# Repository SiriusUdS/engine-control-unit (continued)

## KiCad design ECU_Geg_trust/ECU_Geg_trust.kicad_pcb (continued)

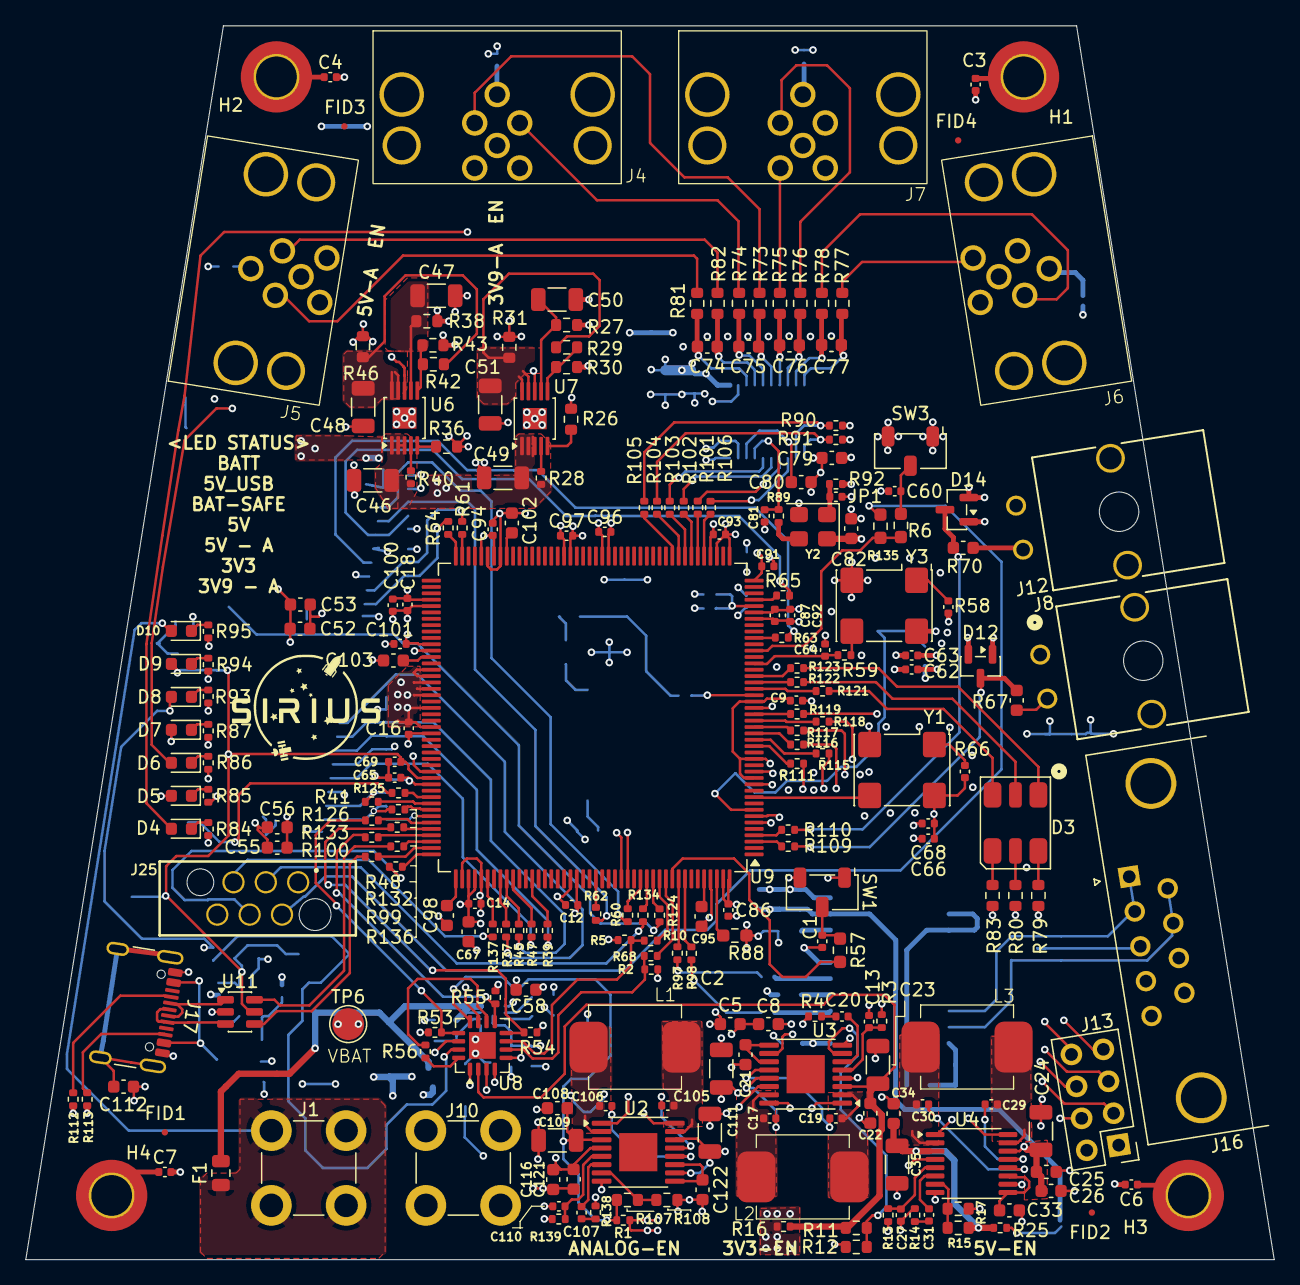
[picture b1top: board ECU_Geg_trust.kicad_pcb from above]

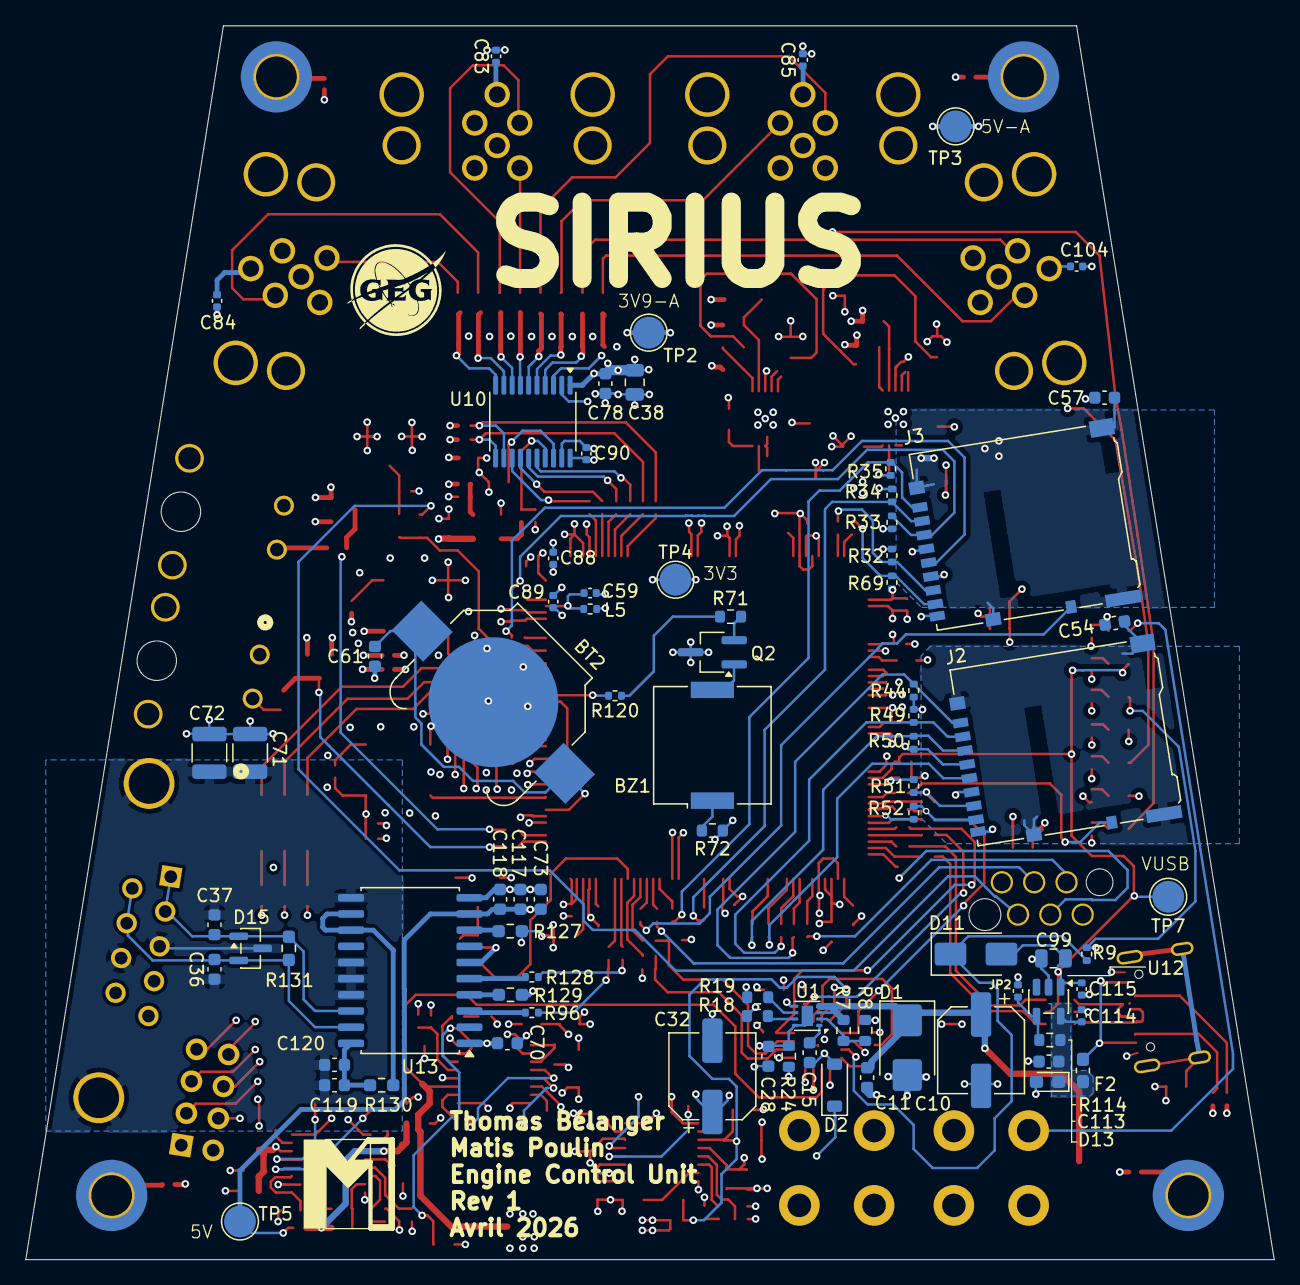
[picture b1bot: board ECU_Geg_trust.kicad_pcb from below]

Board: 6 copper layers, 98.0 x 96.9 mm, 321 parts (80 on the bottom side), 224 nets.

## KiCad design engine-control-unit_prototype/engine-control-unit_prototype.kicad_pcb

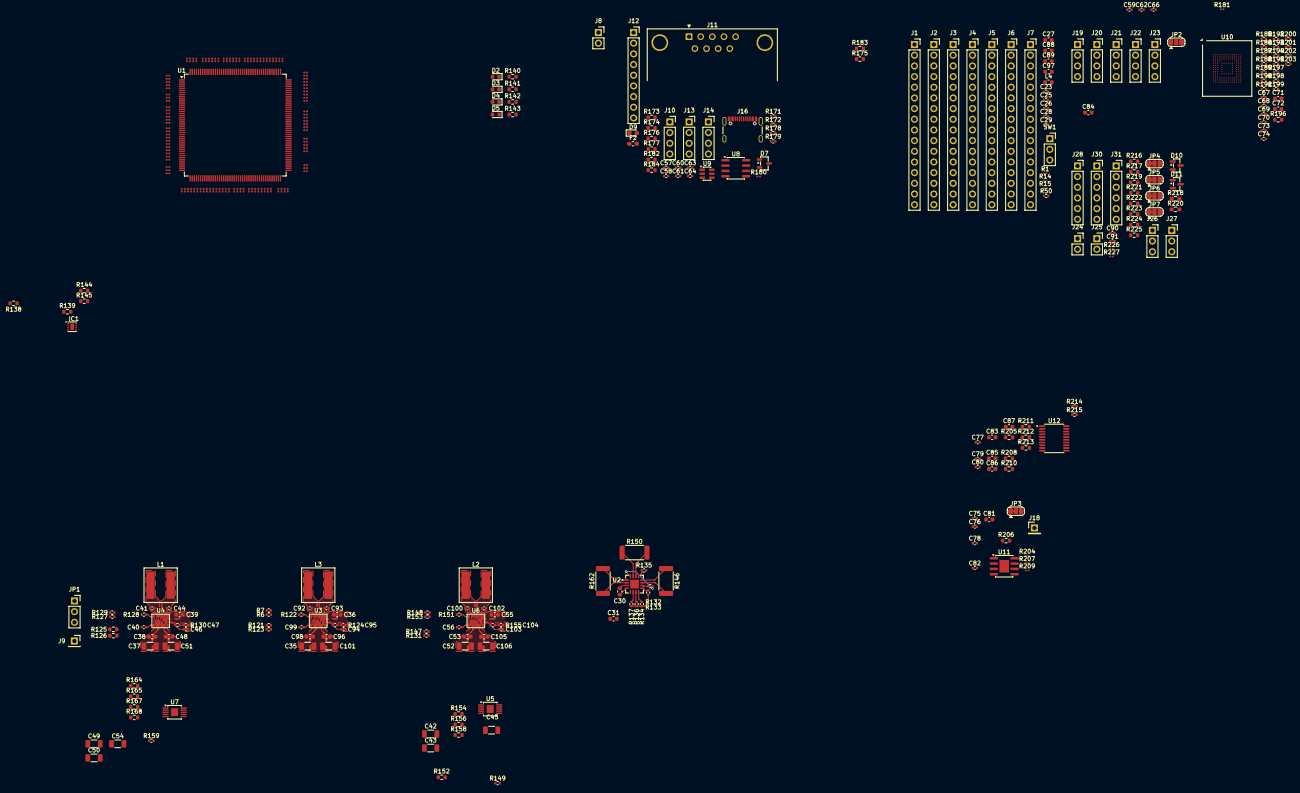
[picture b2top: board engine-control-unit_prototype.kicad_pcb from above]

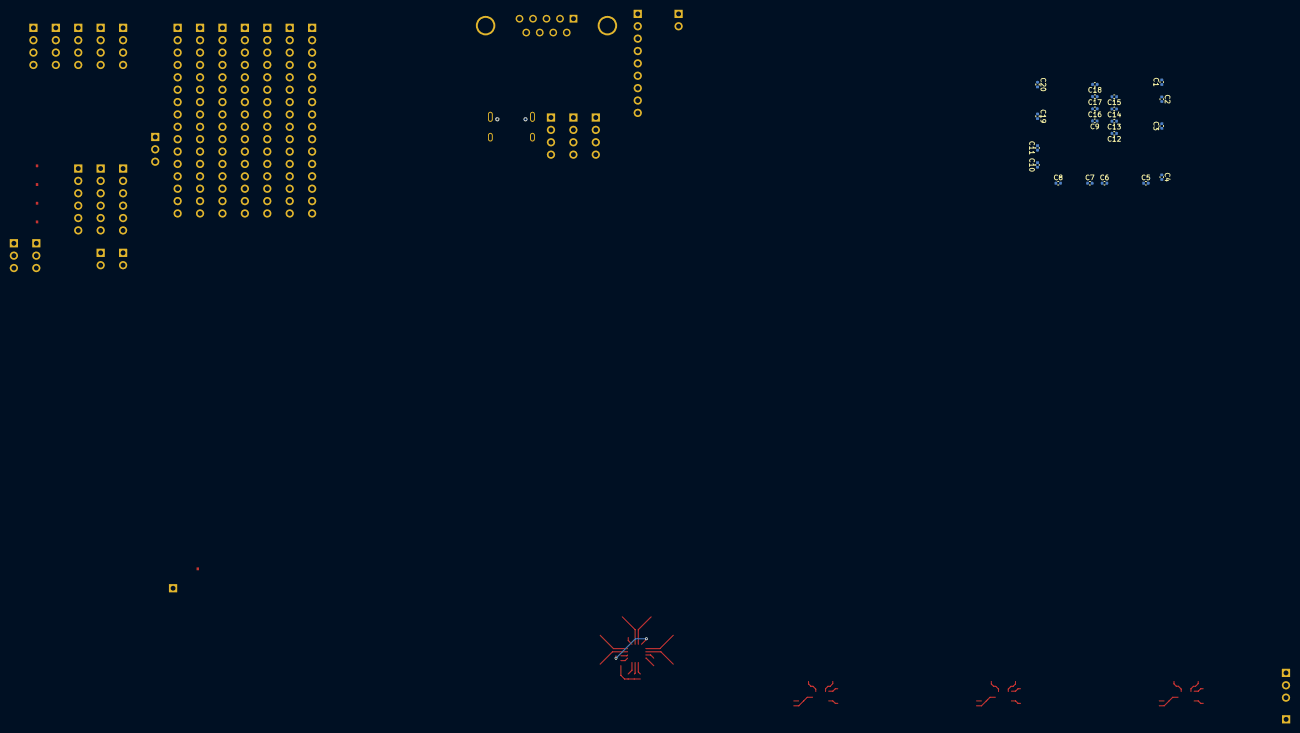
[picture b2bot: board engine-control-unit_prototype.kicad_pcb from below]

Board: 2 copper layers, 381 parts (20 on the bottom side), 374 nets.

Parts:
C1, C2, C3, C4, C5, C6, C7, C8, C9, C10, C11, C12, C13, C14, C15, C16, C17, C18, C19, C20, C23, C25, C26, C28, C29, C57, C58: 100n; C_0402_1005Metric
C27: 2.2u ESR < 600m; C_0603_1608Metric
C30: 0u1; C_0603_1608Metric
C31, C71, C84: 10u; C_0603_1608Metric
C35, C37, C42, C43, C45, C51, C52, C101, C106: C; C_1206_3216Metric
C36, C38, C39, C48, C53, C55, C96, C98, C105: C; C_0603_1608Metric
C40, C41, C44, C56, C92, C93, C99, C100, C102: C; C_0402_1005Metric
C46, C94, C103: 100p; C_0402_1005Metric
C47, C59, C76, C78, C82, C95, C104: ?; C_0402_1005Metric
C49, C50, C54: 4u7; C_1206_3216Metric
C60, C61: DNF; C_0402_1005Metric
C62, C63, C64, C66, C67, C68, C69, C70, C73, C74, C75, C90, C91: 0u1; C_0402_1005Metric
C72: 2.2u; C_0603_1608Metric
C77: 10n; C_0402_1005Metric
C79, C80: 1u; C_0402_1005Metric
C81: DNF; C_0603_1608Metric
C83, C85, C87: 10n; C_0603_1608Metric
C86: 220n; C_0603_1608Metric
C88, C89: 2u2; C_0603_1608Metric
C97: 4u7; C_0603_1608Metric
D2: VBATT+; LED_0603_1608Metric
D3: VDD_10V; LED_0603_1608Metric
D4: VDD_3V3; LED_0603_1608Metric
D5: VDDA_3V3; LED_0603_1608Metric
D7: DNF; SOT-23-3
D9: 6.4V; D_0603_1608Metric_Pad1.05x0.95mm_HandSolder
D10, D11: BAV99; SOT-23
F2: Polyfuse; Fuse_0603_1608Metric_Pad1.05x0.95mm_HandSolder
IC1: TPS259573DSGR; WSON-8-1EP_2x2mm_P0.5mm_EP0.9x1.6mm
J1: PORT_G; PinSocket_1x16_P2.54mm_Vertical
J2: PORT_E; PinSocket_1x16_P2.54mm_Vertical
J3: PORT_F; PinSocket_1x16_P2.54mm_Vertical
J4: PORT_A; PinSocket_1x16_P2.54mm_Vertical
J5: PORT_B; PinSocket_1x16_P2.54mm_Vertical
J6: PORT_D; PinSocket_1x16_P2.54mm_Vertical
J7: PORT_C; PinSocket_1x16_P2.54mm_Vertical
J8: 2S_18650; PinSocket_1x02_P2.54mm_Vertical
J9: EXT_BATT; PinSocket_1x01_P2.54mm_Vertical
J10: I2C; PinSocket_1x04_P2.54mm_Vertical
J11: CANFD; DSUB-9_Pins_Horizontal_P2.77x2.84mm_EdgePinOffset7.70mm_Hou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
J12: ADXL345; PinSocket_1x09_P2.54mm_Vertical
J13: MAG_CONN_1; PinSocket_1x04_P2.54mm_Vertical
J14: MAG_CONN_2; PinSocket_1x04_P2.54mm_Vertical
J16: USB_C_Receptacle_USB2.0_man; USB_C_Receptacle_GCT_USB4105-xx-A_16P_TopMnt_Horizontal
J18: VREF; PinHeader_1x01_P2.54mm_Vertical
J19: PT1; PinSocket_1x04_P2.54mm_Vertical
J20: PT2; PinSocket_1x04_P2.54mm_Vertical
J21: PT3; PinSocket_1x04_P2.54mm_Vertical
J22: PT4; PinSocket_1x04_P2.54mm_Vertical
J23: PT5; PinSocket_1x04_P2.54mm_Vertical
J24: HEATER_IPA; PinSocket_1x02_P2.54mm_Vertical
J25: HEATER_NOS; PinSocket_1x02_P2.54mm_Vertical
J26: VALVE_IPA; PinSocket_1x03_P2.54mm_Vertical
J27: VALVE_NOS; PinSocket_1x03_P2.54mm_Vertical
J28: NOS ENCODER; PinSocket_1x06_P2.54mm_Vertical
J30: IPA ENCODER; PinSocket_1x06_P2.54mm_Vertical
J31: VCTR_CONN; PinSocket_1x06_P2.54mm_Vertical
JP1: BATT; PinSocket_1x03_P2.54mm_Vertical
JP2: 3V3 / 10V; SolderJumper-3_P1.3mm_Open_RoundedPad1.0x1.5mm
JP3: PIN / GND; SolderJumper-3_P1.3mm_Bridged12_RoundedPad1.0x1.5mm
JP4, JP5, JP6, JP7: CONN / BOARD; SolderJumper-3_P1.3mm_Bridged12_RoundedPad1.0x1.5mm
L1, L2, L3: L; L_Coilcraft_XAL7070-XXX
L4: L_Ferrite; L_0603_1608Metric
R1, R2, R3, R4, R5, R8, R9, R10, R11, R12, R13, R14, R15, R16, R17, R18, R19, R20, R21, R22, R23, R24, R25, R26, R27, R28, R29, R30, R31, R32, R33, R34, R35, R36, R37, R38, R39, R40, R41, R42, R43, R44, R45, R46, R47, R48, R49, R51, R52, R53, R54, R55, R56, R57, R58, R59, R60, R61, R62, R63, R64, R65, R66, R67, R68, R69, R70, R71, R72, R73, R74, R75, R76, R77, R78, R79, R80, R81, R82, R83, R84, R85, R86, R87, R88, R89, R90, R91, R92, R93, R94, R95, R96, R97, R98, R99, R100, R101, R102, R103, R104, R105, R106, R107, R108, R109, R110, R111, R112, R113, R114, R115, R116, R117, R118, R119, R120, R180, R181, R204, R207, R209, R226, R227: 0; R_0201_0603Metric
R6, R7, R50, R131, R147: R_US; R_0402_1005Metric
R121, R123, R127, R129, R148, R153: 2k20; R_0402_1005Metric
R122, R128, R151: 0; R_0402_1005Metric
R124, R130, R155: 27k4; R_0402_1005Metric
R125, R126, R138, R139, R144, R145, R152, R154, R156, R158, R184: R_US; R_0603_1608Metric
R132, R133, R134, R135, R136, R137, R185, R186, R187, R188, R189, R190, R191, R192, R193, R194, R195, R197, R198, R199, R200, R201, R202, R203: 10k; R_0402_1005Metric
R140, R141, R142, R143, R196, R206, R216, R217, R219, R221, R222, R223: ?; R_0603_1608Metric
R146, R150, R162: 10m; R_2512_6332Metric
R149, R159: 200k; R_0402_1005Metric
R164: 453k; R_0603_1608Metric
R165: 510; R_0603_1608Metric
R167: 33k2; R_0603_1608Metric
R168: 49k9; R_0603_1608Metric
R171, R172, R178, R179, R214, R215: 1k; R_0402_1005Metric
R173, R174, R175: 0; R_0603_1608Metric
R176, R177: 60; R_0603_1608Metric
R182, R183: 5.1k; R_0603_1608Metric
R205, R208, R210, R211, R212, R213, R224, R225: 1k; R_0603_1608Metric
R218, R220: 10k; R_0603_1608Metric_Pad0.98x0.95mm_HandSolder
SW1: BOOT; PinSocket_1x03_P2.54mm_Vertical
U1: STM32H747II; LQFP-176_24x24mm_P0.5mm
U2: INA3221; Texas_RGV0016A_VQFN-16-1EP_4x4mm_P0.65mm_EP2.1x2.1mm
U3, U4, U6: TPS55285; WQFN-HR - 15
U5, U7: LT3042xMSE; MSOP-10-1EP_3x3mm_P0.5mm_EP1.68x1.88mm
U8: TCAN337G; SOIC-8_3.9x4.9mm_P1.27mm
U9: USBLC6-2SC6; SOT-23-6
U10: LFBGA-153_11.5x13mm_Layout14x14_P0.5mm
U11: INA826; SOIC-8-1EP_3.9x4.9mm_P1.27mm_EP2.29x3mm
U12: ADS131M04xPW; TSSOP-20_4.4x6.5mm_P0.65mm

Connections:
+BATT1: D2.2 (A), J8.1, J24.1, J25.1, R216.1, R217.1
/ADC/+IN1: J19.2, R204.2
/ADC/+IN2: C77.2, J20.2, R205.2
/ADC/+IN3: C83.2, J21.2, R210.2
/ADC/+IN4: C85.2, J22.2, R212.2
/ADC/+IN5: C87.2, J23.2, R214.2
/ADC/-IN1: J19.3, R209.2
/ADC/-IN2: C77.1, J20.3, R208.2
/ADC/-IN3: C83.1, J21.3, R211.2
/ADC/-IN4: C85.1, J22.3, R213.2
/ADC/-IN5: C87.1, J23.3, R215.2
/ADC/PT1: C81.2, R207.1
/BOOT0: SW1.2 (B), U1.167 (BOOT0)
/COMMUNICATION/ADXL_SCL: J12.9, R179.2
/COMMUNICATION/ADXL_SDA: J12.8, R178.2
/COMMUNICATION/CANH: C60.2, D7.1 (K), J11.7, J13.2, J14.2, R177.1, U8.7 (CANH)
/COMMUNICATION/CANL: C61.2, D7.2 (K), J11.2, J13.3, J14.3, R176.1, U8.6 (CANL)
/COMMUNICATION/I2C_SCL: J10.4, R172.2
/COMMUNICATION/I2C_SDA: J10.3, R171.2
/COMMUNICATION/TCAN_STBY: R175.1, U8.8 (S)
/COMMUNICATION/USB_D+: J16.A6 (D+), J16.B6 (D+), U9.3 (I/O2), U9.4 (I/O2)
/COMMUNICATION/USB_D-: J16.A7 (D-), J16.B7 (D-), U9.1 (I/O1), U9.6 (I/O1)
/CONTROL/IPA_DATA: D10.3 (K), J26.1, JP4.2 (C), JP4.3 (B), R218.1
/CONTROL/IPA_DATA_CONN: J31.2, JP4.1 (A)
/CONTROL/IPA_HEAT: JP6.2 (C), JP6.3 (B), R219.1
/CONTROL/IPA_HEAT_CONN: J31.4, JP6.1 (A)
/CONTROL/NOS_DATA: D11.3 (K), J27.2, JP5.2 (C), JP5.3 (B), R220.1
/CONTROL/NOS_DATA_CONN: J31.3, JP5.1 (A)
/CONTROL/NOS_HEAT: JP7.2 (C), JP7.3 (B), R221.1
/CONTROL/NOS_HEAT_CONN: J31.5, JP7.1 (A)
/NRST: R50.2, U1.33 (NRST)
/POWER/EFUSE_FLT: IC1.6 (~FLT), R139.1
/POWER/L1_L: C41.1, L1.1, U4.6 (SW1)
/POWER/L1_R: C44.1, L1.2, U4.8 (SW2)
/POWER/L2_L: C100.1, L2.1, U6.6 (SW1)
/POWER/L2_R: C102.1, L2.2, U6.8 (SW2)
/POWER/L3_L: C92.1, L3.1, U3.6 (SW1)
/POWER/L3_R: C93.1, L3.2, U3.8 (SW2)
/POWER/PM_CRIT: R133.2, U2.9 (CRITICAL)
/POWER/PM_SCL: R137.2, U2.6 (SCL)
/POWER/PM_SDA: R136.2, U2.7 (SDA)
/POWER/PM_TC: R135.2, U2.13 (TC)
/POWER/PM_WARN: R134.2, U2.8 (WARNING)
/POWER/Psense1_IN+: C96.1, C101.1, R146.1, U2.12 (IN+1), U3.9 (VOUT)
/POWER/Psense2_IN+: C43.1, R150.1, R152.1, U2.15 (IN+2), U5.9 (OUTS), U5.10 (OUT)
/POWER/Psense3_IN+: C50.1, R162.1, R164.1, U2.2 (IN+3), U7.9 (OUTS), U7.10 (OUT)
/POWER/TPS3V3A_SCL: R148.2, U6.2 (SCL)
/POWER/TPS3V3A_SDA: R153.2, U6.3 (SDA)
/POWER/TPS3V3A_VCC: C55.1, U6.13 (VCC)
/POWER/TPS3V3A_VOUT: C42.1, C105.1, C106.1, R149.1, U5.1 (IN), U5.2 (IN), U5.3 (EN/UV), U6.9 (VOUT)
/POWER/TPS3V3_SCL: R121.2, U3.2 (SCL)
/POWER/TPS3V3_SDA: R123.2, U3.3 (SDA)
/POWER/TPS3V3_VCC: C36.1, U3.13 (VCC)
/POWER/TPS10V_SCL: R127.2, U4.2 (SCL)
/POWER/TPS10V_SDA: R129.2, U4.3 (SDA)
/POWER/TPS10V_VCC: C39.1, U4.13 (VCC)
/POWER/TPS10V_VIN: C37.1, C38.1, JP1.2 (C), R125.1, U4.5 (VIN)
/POWER/TPS10V_VOUT: C48.1, C49.1, C51.1, R159.1, U4.9 (VOUT), U7.1 (IN), U7.2 (IN), U7.3 (EN/UV)
/STORAGE/eMMC_CLK: R185.2, U10.M6 (CLK)
/STORAGE/eMMC_CMD: R186.2, U10.M5 (CMD)
/STORAGE/eMMC_DAT0: R187.2, U10.A3 (DAT0)
/STORAGE/eMMC_DAT1: R188.2, U10.A4 (DAT1)
/STORAGE/eMMC_DAT2: R189.2, U10.A5 (DAT2)
/STORAGE/eMMC_DAT3: R190.2, U10.B2 (DAT3)
/STORAGE/eMMC_DAT4: R191.2, U10.B3 (DAT4)
/STORAGE/eMMC_DAT5: R192.2, U10.B4 (DAT5)
/STORAGE/eMMC_DAT6: R193.2, U10.B5 (DAT6)
/STORAGE/eMMC_DAT7: R194.2, U10.B6 (DAT7)
/STORAGE/eMMC_RST: R195.2, U10.K5 (RST_n)
GND: C1.2, C2.2, C3.2, C4.2, C5.2, C6.2, C7.2, C8.2, C9.2, C10.2, C11.2, C12.2, C13.2, C14.2, C15.2, C16.2, C17.2, C18.2, C19.2, C20.2, C23.2, C25.2, C26.2, C27.2, C28.2, C29.2, C30.2, C31.1, C35.2, C36.2, C37.2, C38.2, C39.2, C40.2, C42.2, C43.2, C45.2, C46.2, C47.2, C48.2, C49.2, C50.2, C51.2, C52.2, C53.2, C54.2, C55.2, C56.2, C57.1, C58.2, C59.1, C60.1, C61.1, C62.1, C63.1, C64.2, C66.1, C67.2, C68.2, C69.2, C70.2, C71.2, C72.2, C73.2, C74.1, C75.1, C76.2, C79.1, C80.2, C81.1, C82.1, C84.1, C86.1, C88.2, C89.2, C90.2, C91.2, C94.2, C95.2, C96.2, C97.1, C98.2, C99.2, C101.2, C103.2, C104.2, C105.2, C106.2, D7.3 (A), D9.2 (A), D10.1 (K), D11.1 (K), IC1.8 (GND_1), IC1.9 (GND_2), J8.2, J10.1, J11.3, J13.4, J14.4, J16.A1 (GND), J16.A12 (GND), J16.B1 (GND), J16.B12 (GND), J19.4, J20.4, J21.4, J22.4, J23.4, J26.3, J27.3, J28.6, J30.6, JP3.1 (A), R7.2, R122.2, R126.2, R128.2, R140.2, R141.2, R142.2, R143.2, R144.2, R145.2, R147.2, R151.2, R154.2, R156.2, R158.2, R165.2, R167.2, R168.2, R181.1, R182.1, R183.2, R184.2, R196.1, R218.2, R220.2, R222.1, R223.1, R227.2, SW1.1 (A), U1.6 (VSS), U1.12 (VSS), U1.14 (VSSSMPS), U1.24 (VSS), U1.38 (VSSA), U1.45 (VSS), U1.47 (VSS), U1.64 (VSS), U1.70 (VSS), U1.81 (VSS), U1.83 (VSS), U1.93 (VSS), U1.100 (VSS), U1.105 (VSSDSI), U1.109 (VSSDSI), U1.112 (VSS), U1.119 (VSS), U1.134 (VSS), U1.137 (VSS), U1.151 (VSS), U1.159 (VSS), U1.173 (VSS), U1.174 (PDR_ON), U2.3 (GND), U2.5 (A0), U2.17 (EP), U3.7 (PGND), U3.12 (AGND), U4.7 (PGND), U4.12 (AGND), U5.8 (GND), U5.11 (GND), U6.7 (PGND), U6.12 (AGND), U7.8 (GND), U7.11 (GND), U8.2 (GND), U9.2 (GND), U10.A6 (VSS), U10.C4 (VSSQ), U10.E7 (VSS), U10.G5 (VSS), U10.H10 (VSS), U10.J5 (VSS), U10.K8 (VSS), U10.N2 (VSSQ), U10.N5 (VSSQ), U10.P4 (VSSQ), U10.P6 (VSSQ), U11.5 (GND), U12.2 (AGND), U12.19 (DGND)
unnamed: C47.1, R130.2
unnamed: C62.2, R176.2, R177.2
unnamed: C95.1, R124.2
unnamed: C104.1, R155.2
unnamed: D2.1 (K), R140.1
unnamed: D3.1 (K), R141.1
unnamed: D4.1 (K), R142.1
unnamed: D5.1 (K), R143.1
unnamed: IC1.3 (IN_1), IC1.4 (IN_2), R138.1
unnamed: D9.1 (K), F2.2
unnamed: F2.1, J16.A4 (VBUS), J16.A9 (VBUS), J16.B4 (VBUS), J16.B9 (VBUS)
unnamed: IC1.7 (ILM), R145.1
unnamed: IC1.2 (~EN/OVLO), R138.2, R144.1
unnamed: J1.1, R2.1
unnamed: J1.2, R4.1
unnamed: J1.3, R8.1
unnamed: J1.4, R10.1
unnamed: J1.5, R12.1
unnamed: J1.6, R16.1
unnamed: J1.7, R18.1
unnamed: J1.8, R20.1
unnamed: J1.9, R22.1
unnamed: J1.10, R24.1
unnamed: J1.11, R26.1
unnamed: J1.12, R28.1
unnamed: J1.13, R30.1
unnamed: J1.14, R32.1
unnamed: J1.15, R34.1
unnamed: J1.16, R36.1
unnamed: J2.1, R3.2
unnamed: J2.2, R5.2
unnamed: J2.3, R9.2
unnamed: J2.4, R11.2
unnamed: J2.5, R13.2
unnamed: J2.6, R17.2
unnamed: J2.7, R19.2
unnamed: J2.8, R21.2
unnamed: J2.9, R23.2
unnamed: J2.10, R25.2
unnamed: J2.11, R27.2
unnamed: J2.12, R29.2
unnamed: J2.13, R31.2
unnamed: J2.14, R33.2
unnamed: J2.15, R35.2
unnamed: J2.16, R37.2
unnamed: J3.1, R38.1
unnamed: J3.2, R40.1
unnamed: J3.3, R42.1
unnamed: J3.4, R44.1
unnamed: J3.5, R46.1
unnamed: J3.6, R48.1
unnamed: J3.7, R51.1
unnamed: J3.8, R53.1
unnamed: J3.9, R56.1
unnamed: J3.10, R59.1
unnamed: J3.11, R61.1
unnamed: J3.12, R63.1
unnamed: J3.13, R65.1
unnamed: J3.14, R67.1
unnamed: J3.15, R69.1
unnamed: J3.16, R71.1
unnamed: J4.1, R39.2
unnamed: J4.2, R41.2
unnamed: J4.3, R43.2
unnamed: J4.4, R45.2
unnamed: J4.5, R47.2
unnamed: J4.6, R49.2
unnamed: J4.7, R52.2
unnamed: J4.8, R54.2
unnamed: J4.9, R57.2
unnamed: J4.10, R60.2
unnamed: J4.11, R62.2
unnamed: J4.12, R64.2
unnamed: J4.13, R66.2
unnamed: J4.14, R68.2
unnamed: J4.15, R70.2
unnamed: J4.16, R72.2
unnamed: J5.1, R73.1
unnamed: J5.2, R75.1
unnamed: J5.3, R77.1
unnamed: J5.4, R79.1
unnamed: J5.5, R81.1
unnamed: J5.6, R83.1
unnamed: J5.7, R85.1
unnamed: J5.8, R87.1
unnamed: J5.9, R89.1
unnamed: J5.10, R91.1
unnamed: J5.11, R93.1
unnamed: J5.12, R95.1
unnamed: J5.13, R97.1
unnamed: J5.14, R99.1
unnamed: J5.15, R101.1
unnamed: J5.16, R103.1
unnamed: J6.1, R74.2
unnamed: J6.2, R76.2
unnamed: J6.3, R78.2
unnamed: J6.4, R80.2
unnamed: J6.5, R82.2
unnamed: J6.6, R84.2
unnamed: J6.7, R86.2
unnamed: J6.8, R88.2
unnamed: J6.9, R90.2
unnamed: J6.10, R92.2
unnamed: J6.11, R94.2
unnamed: J6.12, R96.2
unnamed: J6.13, R98.2
unnamed: J6.14, R100.2
unnamed: J6.15, R102.2
unnamed: J6.16, R104.2
unnamed: J7.1, R105.1
unnamed: J7.2, R106.1
unnamed: J7.3, R107.1
unnamed: J7.4, R108.1
unnamed: J7.5, R109.1
unnamed: J7.6, R110.1
unnamed: J7.7, R111.1
unnamed: J7.8, R112.1
unnamed: J7.9, R113.1
unnamed: J7.10, R114.1
unnamed: J7.11, R115.1
unnamed: J7.12, R116.1
unnamed: J7.13, R117.1
unnamed: J7.14, R118.1
unnamed: J7.15, R119.1
unnamed: J7.16, R120.1
unnamed: J9.1, JP1.3 (B)
unnamed: C63.2, J11.0 (PAD), J11.5
unnamed: J12.1, R181.2
unnamed: J12.2, R180.2
unnamed: J16.A5 (CC1), R182.2
unnamed: J16.B5 (CC2), R183.1
unnamed: C66.2, J16.S1 (SHIELD)
unnamed: J18.1, JP3.3 (B)
unnamed: J31.1, R226.2
unnamed: J31.6, R227.1
unnamed: JP3.2 (C), U11.6 (REF)
unnamed: R55.1, U1.31 (PH0)
unnamed: R58.1, U1.32 (PH1)
unnamed: R39.1, U1.41 (PA0)
unnamed: R41.1, U1.42 (PA1)
unnamed: R43.1, U1.43 (PA2)
unnamed: R45.1, U1.46 (PA3)
unnamed: R47.1, U1.49 (PA4)
unnamed: R49.1, U1.50 (PA5)
unnamed: R52.1, U1.51 (PA6)
unnamed: R54.1, U1.52 (PA7)
unnamed: R57.1, U1.127 (PA8)
unnamed: R60.1, U1.128 (PA9)
unnamed: R62.1, U1.129 (PA10)
unnamed: R64.1, U1.130 (PA11)
unnamed: R66.1, U1.131 (PA12)
unnamed: R68.1, U1.132 (PA13)
unnamed: R70.1, U1.138 (PA14)
unnamed: R72.1, U1.139 (PA15)
unnamed: R3.1, U1.170 (PE0)
unnamed: R5.1, U1.171 (PE1)
unnamed: R9.1, U1.1 (PE2)
unnamed: R11.1, U1.2 (PE3)
unnamed: R13.1, U1.3 (PE4)
unnamed: R17.1, U1.4 (PE5)
unnamed: R19.1, U1.5 (PE6)
unnamed: R21.1, U1.67 (PE7)
unnamed: R23.1, U1.68 (PE8)
unnamed: R25.1, U1.69 (PE9)
unnamed: R27.1, U1.72 (PE10)
unnamed: R29.1, U1.73 (PE11)
unnamed: R31.1, U1.74 (PE12)
unnamed: R33.1, U1.75 (PE13)
unnamed: R35.1, U1.76 (PE14)
unnamed: R37.1, U1.77 (PE15)
unnamed: R38.2, U1.18 (PF0)
unnamed: R40.2, U1.19 (PF1)
unnamed: R42.2, U1.20 (PF2)
unnamed: R44.2, U1.21 (PF3)
unnamed: R46.2, U1.22 (PF4)
unnamed: R48.2, U1.23 (PF5)
unnamed: R51.2, U1.26 (PF6)
unnamed: R53.2, U1.27 (PF7)
unnamed: R56.2, U1.28 (PF8)
unnamed: R59.2, U1.29 (PF9)
unnamed: R61.2, U1.30 (PF10)
unnamed: R63.2, U1.58 (PF11)
unnamed: R65.2, U1.59 (PF12)
unnamed: R67.2, U1.60 (PF13)
unnamed: R69.2, U1.61 (PF14)
unnamed: R71.2, U1.62 (PF15)
unnamed: R2.2, U1.63 (PG0)
unnamed: R4.2, U1.66 (PG1)
unnamed: R8.2, U1.110 (PG2)
unnamed: R10.2, U1.111 (PG3)
unnamed: R12.2, U1.114 (PG4)
unnamed: R16.2, U1.115 (PG5)
unnamed: R18.2, U1.116 (PG6)
unnamed: R20.2, U1.117 (PG7)
unnamed: R22.2, U1.118 (PG8)
unnamed: R24.2, U1.153 (PG9)
unnamed: R26.2, U1.154 (PG10)
unnamed: R28.2, U1.155 (PG11)
unnamed: R30.2, U1.156 (PG12)
unnamed: R32.2, U1.157 (PG13)
unnamed: R34.2, U1.158 (PG14)
unnamed: R36.2, U1.161 (PG15)
unnamed: R73.2, U1.55 (PB0)
unnamed: R75.2, U1.56 (PB1)
unnamed: R77.2, U1.57 (PB2)
unnamed: R79.2, U1.162 (PB3)
unnamed: R81.2, U1.163 (PB4)
unnamed: R83.2, U1.164 (PB5)
unnamed: R85.2, U1.165 (PB6)
unnamed: R87.2, U1.166 (PB7)
unnamed: R89.2, U1.168 (PB8)
unnamed: R91.2, U1.169 (PB9)
unnamed: R93.2, U1.78 (PB10)
unnamed: R95.2, U1.79 (PB11)
unnamed: R97.2, U1.85 (PB12)
unnamed: R99.2, U1.86 (PB13)
unnamed: R101.2, U1.87 (PB14)
unnamed: R103.2, U1.88 (PB15)
unnamed: R105.2, U1.34 (PC0)
unnamed: R106.2, U1.35 (PC1)
unnamed: R107.2, U1.36 (PC2_C)
unnamed: R108.2, U1.37 (PC3_C)
unnamed: R109.2, U1.53 (PC4)
unnamed: R110.2, U1.54 (PC5)
unnamed: R111.2, U1.122 (PC6)
unnamed: R112.2, U1.123 (PC7)
unnamed: R113.2, U1.124 (PC8)
unnamed: R114.2, U1.125 (PC9)
unnamed: R115.2, U1.140 (PC10)
unnamed: R116.2, U1.141 (PC11)
unnamed: R117.2, U1.142 (PC12)
unnamed: R118.2, U1.9 (PC13)
unnamed: R119.2, U1.10 (PC14)
unnamed: R120.2, U1.11 (PC15)
unnamed: R74.1, U1.143 (PD0)
unnamed: R76.1, U1.144 (PD1)
unnamed: R78.1, U1.145 (PD2)
unnamed: R80.1, U1.146 (PD3)
unnamed: R82.1, U1.147 (PD4)
unnamed: R84.1, U1.148 (PD5)
unnamed: R86.1, U1.149 (PD6)
unnamed: R88.1, U1.150 (PD7)
unnamed: R90.1, U1.89 (PD8)
unnamed: R92.1, U1.90 (PD9)
unnamed: R94.1, U1.91 (PD10)
unnamed: R96.1, U1.94 (PD11)
unnamed: R98.1, U1.95 (PD12)
unnamed: R100.1, U1.96 (PD13)
unnamed: R102.1, U1.97 (PD14)
unnamed: R104.1, U1.98 (PD15)
unnamed: R132.2, U2.10 (PV)
unnamed: R132.1, U2.16 (VPU)
unnamed: C92.2, U3.15 (BOOT1)
unnamed: C93.2, U3.14 (BOOT2)
unnamed: C94.1, R124.1, U3.11 (COMP)
unnamed: C99.1, R6.2, R7.1, U3.4 (EN/UVLO)
unnamed: R122.1, U3.1 (MODE)
unnamed: C41.2, U4.15 (BOOT1)
unnamed: C44.2, U4.14 (BOOT2)
unnamed: C46.1, R130.1, U4.11 (COMP)
unnamed: C40.1, R125.2, R126.1, U4.4 (EN/UVLO)
unnamed: R128.1, U4.1 (MODE)
unnamed: R154.1, U5.5 (ILIM)
unnamed: R149.2, U5.4 (PG)
unnamed: R152.2, R158.1, U5.6 (PGFB)
unnamed: C45.1, R156.1, U5.7 (SET)
unnamed: C100.2, U6.15 (BOOT1)
unnamed: C102.2, U6.14 (BOOT2)
unnamed: C103.1, R155.1, U6.11 (COMP)
unnamed: C56.1, R131.2, R147.1, U6.4 (EN/UVLO)
unnamed: R151.1, U6.1 (MODE)
unnamed: R165.1, U7.5 (ILIM)
unnamed: R159.2, U7.4 (PG)
unnamed: R164.2, R168.1, U7.6 (PGFB)
unnamed: C54.1, R167.1, U7.7 (SET)
unnamed: R174.2, U8.4 (RXD)
unnamed: C59.2, R173.2, U8.1 (TXD)
unnamed: R196.2, U10.H5 (DS)
unnamed: C76.1, C78.2, R204.1, U11.4 (+)
unnamed: C78.1, C82.2, R209.1, U11.1 (-)
unnamed: R206.1, U11.2 (RG+)
unnamed: R206.2, U11.3 (RG-)
unnamed: R207.2, U11.7 (VOUT)
unnamed: R208.1, U12.4 (AIN0N)
unnamed: R205.1, U12.3 (AIN0P)
unnamed: R211.1, U12.5 (AIN1N)
unnamed: R210.1, U12.6 (AIN1P)
unnamed: R213.1, U12.8 (AIN2N)
unnamed: R212.1, U12.7 (AIN2P)
unnamed: R215.1, U12.9 (AIN3N)
unnamed: R214.1, U12.10 (AIN3P)
unnamed: C86.2, U12.18 (CAP)
VBAT_SAFE: C35.1, C52.1, C53.1, C98.1, IC1.5 (OUT), JP1.1 (A), R6.1, R131.1, U3.5 (VIN), U6.5 (VIN)
VCAP: C88.1, C89.1, U1.80 (VCAP), U1.133 (VCAP), U1.172 (VCAP)
VCAPDSI: C26.1, C27.1, U1.101 (VCAPDSI)
VDD33_USB: C28.1, U1.121 (VDD33_USB)
VDD50_USB: C29.1, C64.1, U1.120 (VDD50_USB), U9.5 (VBUS)
VDDA: C75.2, C84.2, JP2.2 (C), U11.8 (V+)
VDDA_3V3: C79.2, D5.2 (A), JP2.1 (A), L4.1, R1.1, R150.2, U2.14 (IN-2), U12.1 (AVDD)
VDDA_MCU: C23.1, R15.2, U1.40 (VDDA)
VDD_3V3: C30.1, C31.2, C57.2, C58.1, C67.1, C68.1, C69.1, C70.1, C71.1, C72.1, C74.2, C80.1, C90.1, C91.1, D4.2 (A), D10.2 (A), D11.2 (A), J10.2, J28.3, J30.3, L4.2, R14.2, R15.1, R121.1, R123.1, R127.1, R129.1, R133.1, R134.1, R135.1, R136.1, R137.1, R139.2, R146.2, R148.1, R153.1, R171.1, R172.1, R175.2, R178.1, R179.1, R180.1, R185.1, R186.1, R187.1, R188.1, R189.1, R190.1, R191.1, R192.1, R193.1, R194.1, R195.1, R197.1, R198.1, R199.1, R200.1, R201.1, R202.1, R203.1, R224.1, R226.1, U2.4 (VS), U2.11 (IN-1), U8.3 (VCC), U10.C2 (VDDI), U10.C6 (VCCQ), U10.E6 (VCC), U10.F5 (VCC), U10.J10 (VCC), U10.K9 (VCC), U10.M4 (VCCQ), U10.N4 (VCCQ), U10.P3 (VCCQ), U10.P5 (VCCQ), U12.20 (DVDD)
VDD_10V: D3.2 (A), J19.1, J20.1, J21.1, J22.1, J23.1, JP2.3 (B), R162.2, U2.1 (IN-3)
VDD_MCU: C1.1, C2.1, C3.1, C4.1, C5.1, C6.1, C7.1, C8.1, C9.1, C10.1, C11.1, C12.1, C13.1, C14.1, C15.1, C16.1, C17.1, C18.1, C19.1, C20.1, C97.2, R14.1, R50.1, SW1.3 (C), U1.7 (VDD), U1.13 (VDD), U1.16 (VDDSMPS), U1.25 (VDD), U1.44 (VDD), U1.48 (VDD), U1.65 (VDD), U1.71 (VDD), U1.82 (VDDLDO), U1.84 (VDD), U1.92 (VDD), U1.99 (VDD), U1.113 (VDD), U1.126 (VDD), U1.135 (VDDLDO), U1.136 (VDD), U1.152 (VDD), U1.160 (VDD), U1.175 (VDDLDO), U1.176 (VDD)
VREF+: C25.1, R1.2, U1.39 (VREF+)

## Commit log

2025-12-03 Add files via upload
    Added eval board files from first repos
2025-12-03 Add files via upload
    Renamed CANopus project to engine-control-unit_prototype
2025-12-04 Added power circuitry without components values
2026-01-07 Modified SD card Fixed INA826 decoupling caps Removed reset button Added Ports connectors (headers for ease of access)
2026-01-08 Removed bloat libraries Changed symbols for Sirius custom library Changed layout for one page
2026-01-08 Removed some more bloated libraries
2026-01-08 Removed subsheets
2026-01-09 Modif eMMC, devrait etre good (A review avec geg).
2026-01-12 Added ringing resistor for eMMC
2026-01-12 Fixed awkward sd card pull-up resistors placement
2026-01-12 Added TPS55285 circuits
2026-01-12 Fixed layout a bit
2026-01-12 More layout cleanup
2026-01-12 Added ADXL345 Accelerometer
2026-01-12 Added valve control
2026-01-13 Changed location of PINS TO MAP to PORTS Changed location of JTAG to USB-C/PROG Added Thermistors (ca parait du que le cours d'innov est intéressant ?)
2026-01-13 Added magnetic connector
2026-01-19 Fixed some of the issues from design review Added heater circuit Added buzzer circuit (I know layout wierd rn, it will be fixed later)
2026-01-20 Added test points
2026-01-26 Some fixes Back to subsheets Missing new ADC boost ldo for 3V3 now
2026-01-26 Fixed some issues Layout back to subsheets Modified buck-boost 3V3 to boost 3V5 -> LDO 3V3 Need to add encoders and Matis ADC
2026-01-28 Added subsheets
2026-02-16 Added control page Revisited power tree (VDDA_3V3 and VDD_3V3) Bunch of other fixes
2026-02-16 Fixed inverted LED diodes (oops) Replaced 3x INA219 with INA3221
2026-02-16 Added magnetic encoders Added optional external valve control connector
2026-02-17 VDD_3V3 is now VDD_3V6 (Removed LDO) LEDs now have the right symbol (oops x2)
2026-02-23 Started layout Added some footprints
2026-02-26 Added better LIB tree Continued PCB layout Some fixes Added chip for protection
2026-02-26 Added MCU bulk cap Added RST button Fixed VDDA_MCU
2026-02-26 Continued layout
2026-03-07 ajout de page root
2026-04-01 Version post Pascal
    reste quelques truc a ajouter sur le silkscreen, ne pas oublier logo Pascal
2026-04-01 modification de quelques traces
2026-04-08 tite modif sur les traces interne
2026-04-08 ajout des logos
2026-04-08 En gros aucun ajout depuis le dernier commit... Un ti deplacement de trace parci par la
2026-04-09 Modification des nets de tensions sur le schematique
2026-04-09 Ajout de certain calculs pour eventuellement calculer esl feedback resistors
2026-04-13 arthur bom
2026-04-17 arthur
2026-04-27 Commentaires matis
2026-04-28 Modification de l'ADC pour un autre qui fonctionne
2026-05-05 Reste a faire le BOM
2026-05-06 BOM pas mal finis reste la valid
2026-05-30 board commandé
2026-06-02 board pt?
2026-06-02 Update .history submodule pointer
2026-06-02 test2
